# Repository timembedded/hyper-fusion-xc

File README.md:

# hyper-fusion-xc
MSX HyperFusion XC

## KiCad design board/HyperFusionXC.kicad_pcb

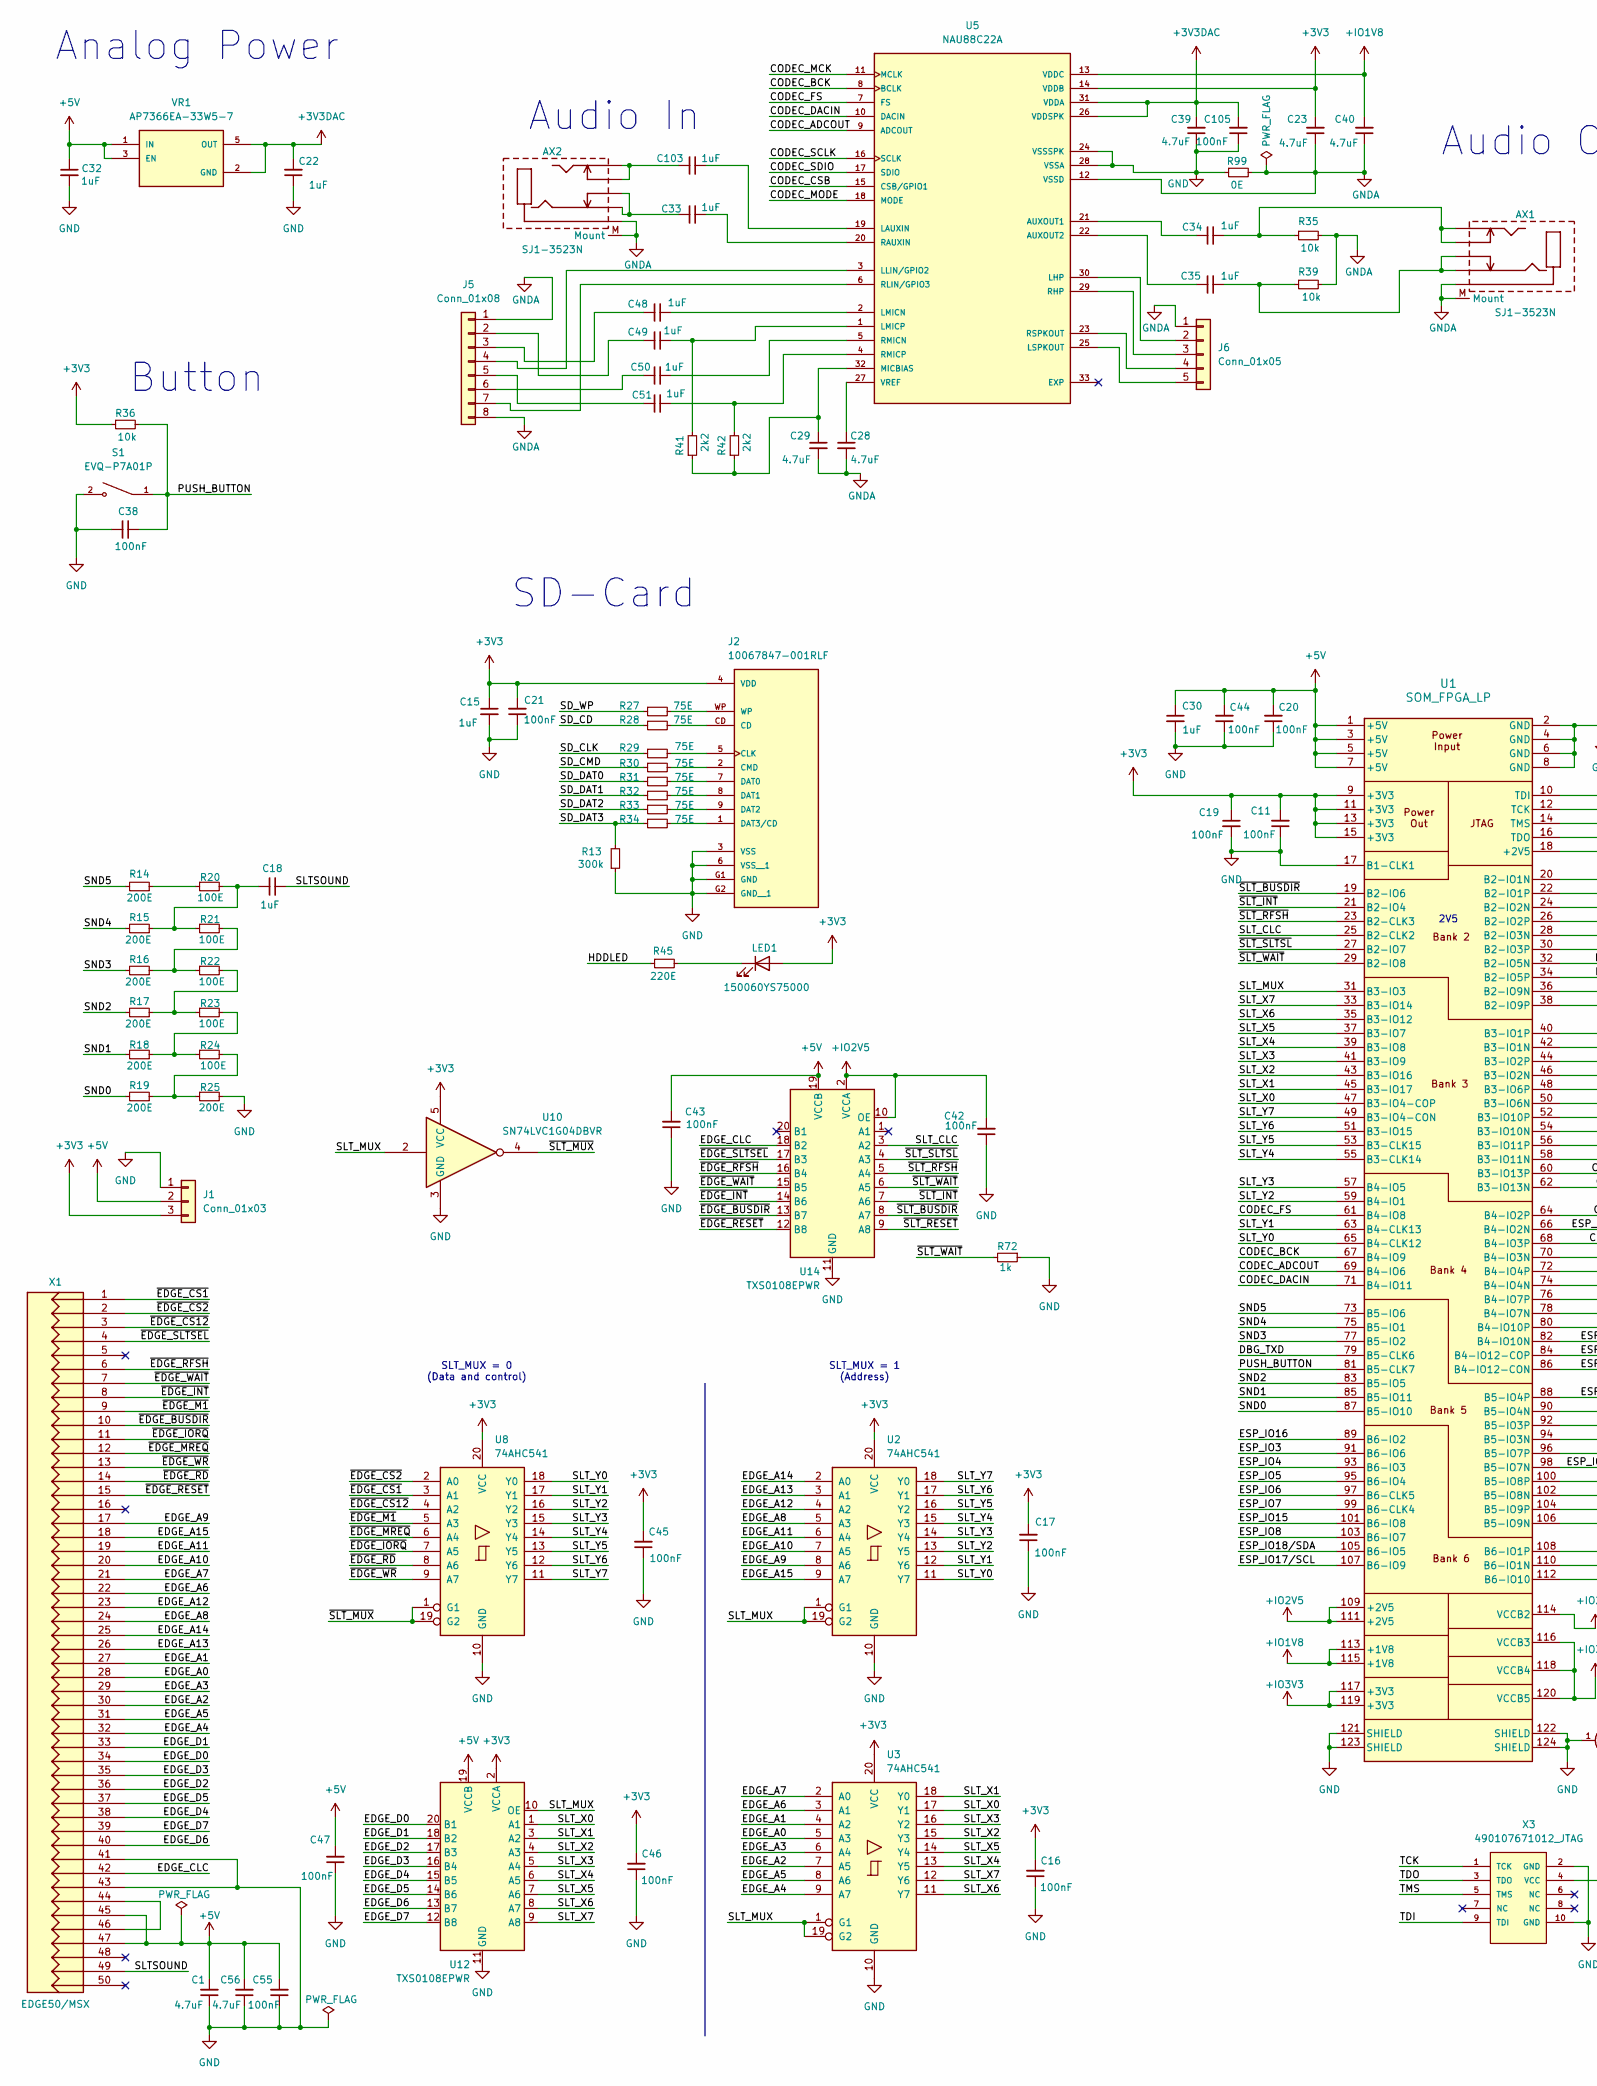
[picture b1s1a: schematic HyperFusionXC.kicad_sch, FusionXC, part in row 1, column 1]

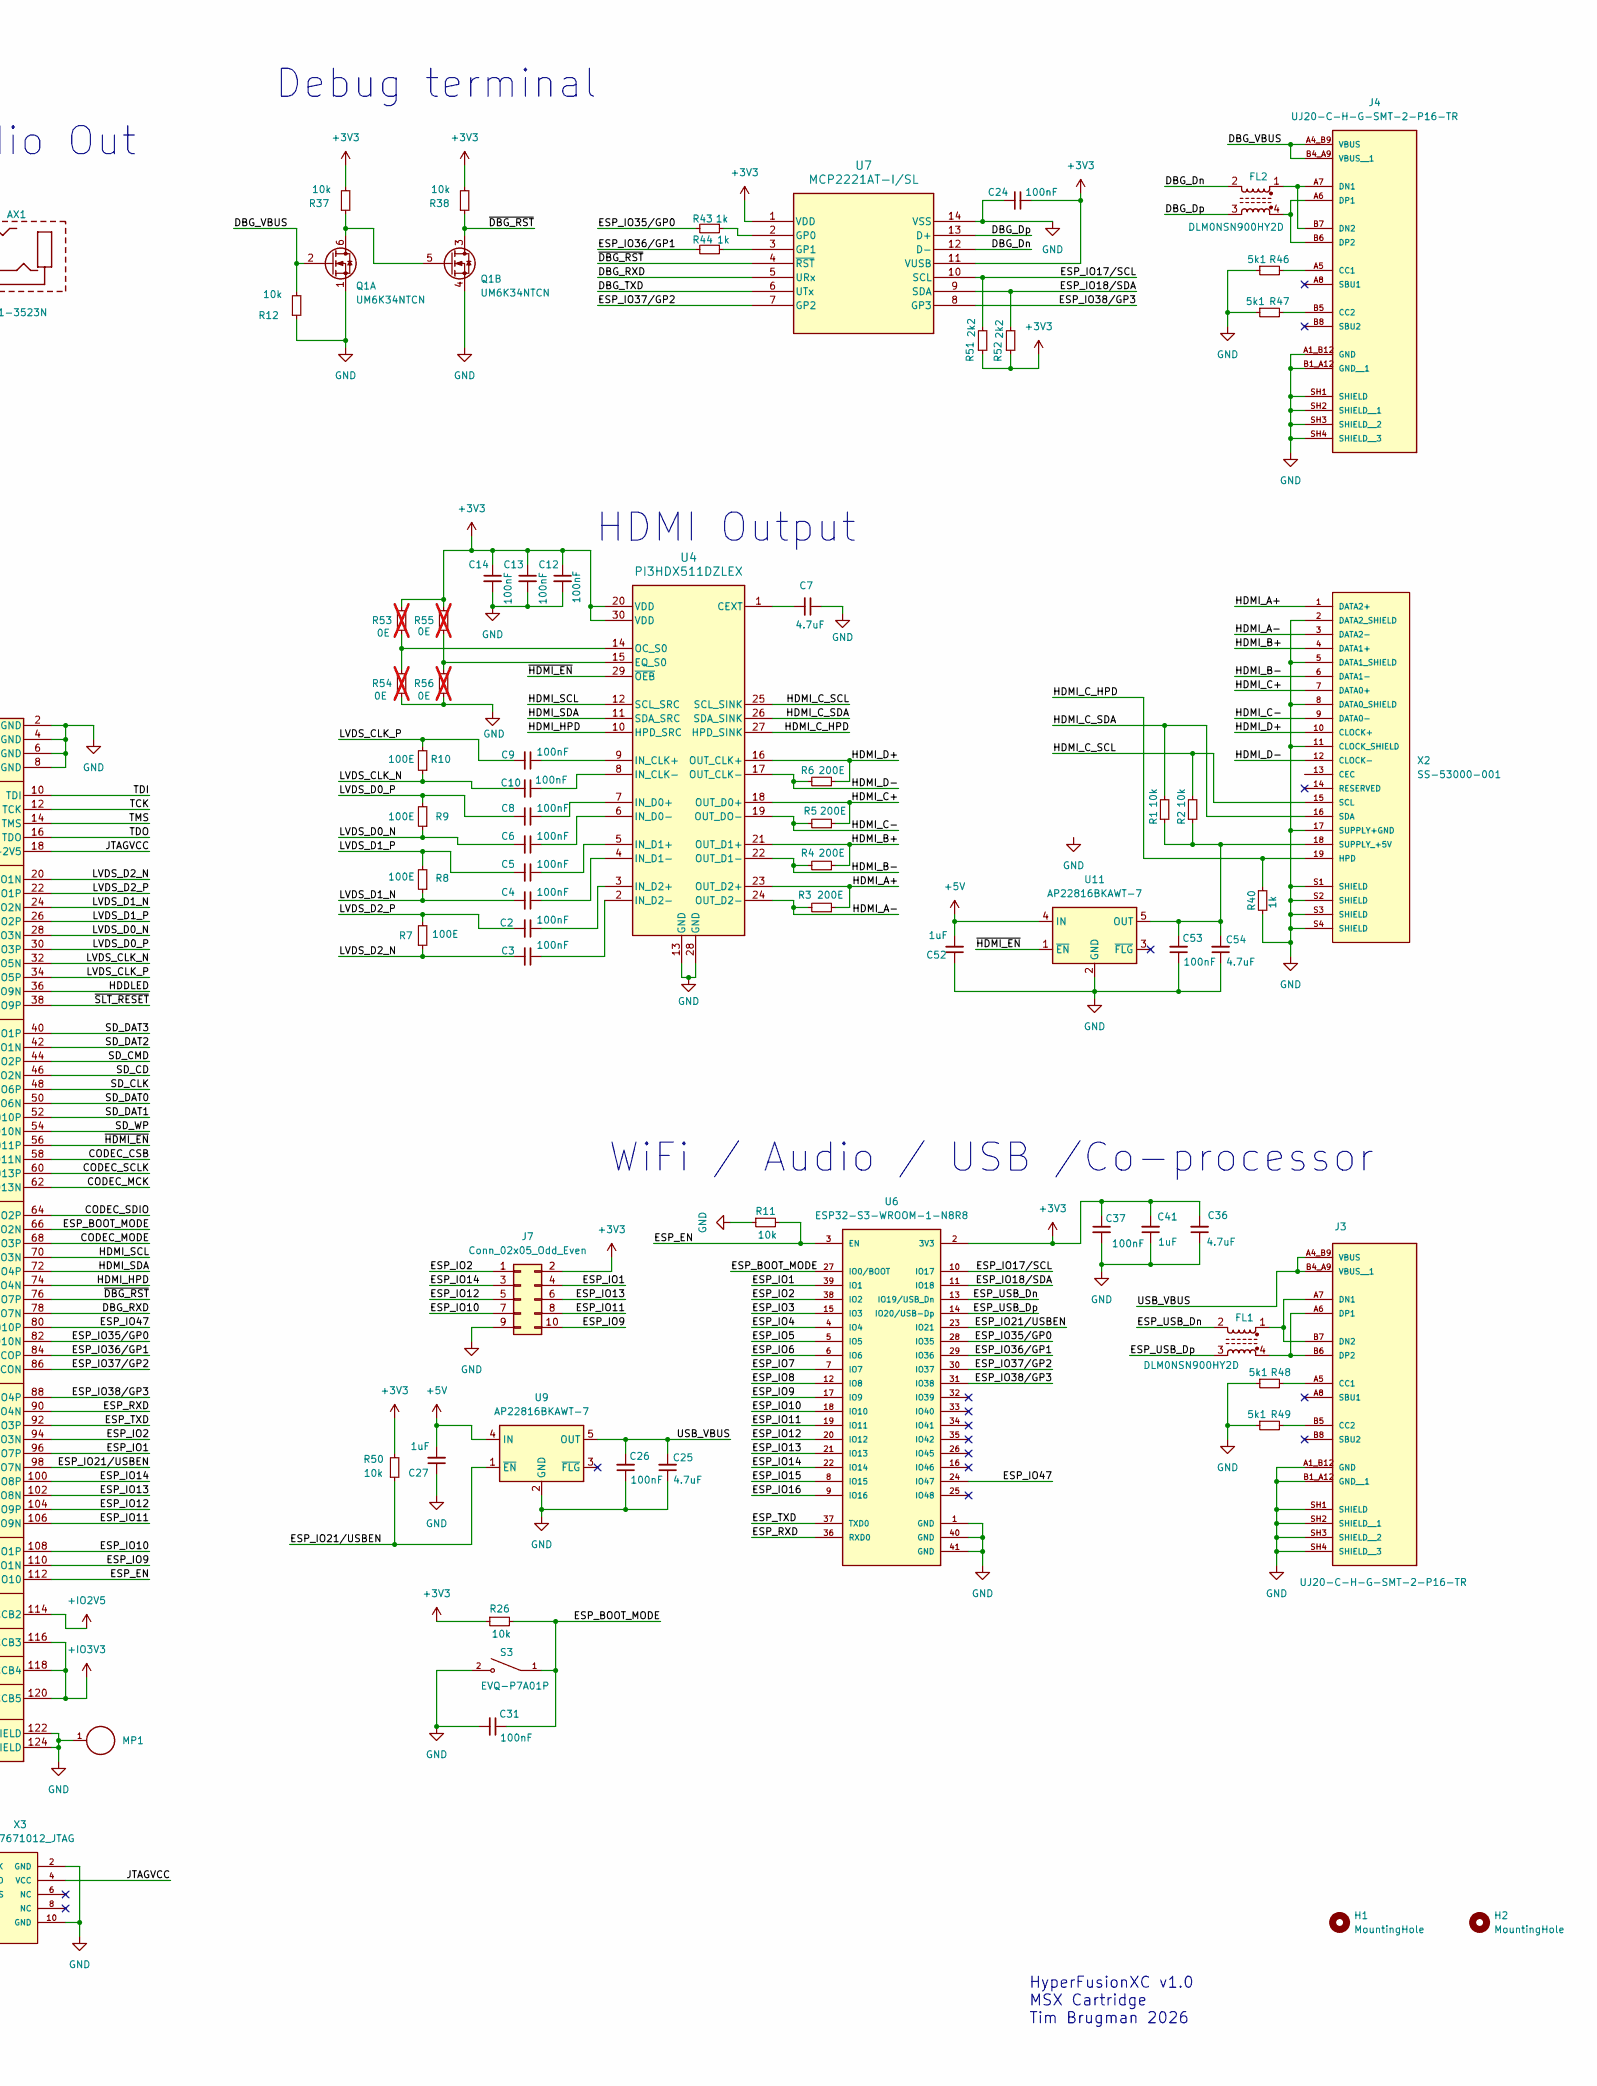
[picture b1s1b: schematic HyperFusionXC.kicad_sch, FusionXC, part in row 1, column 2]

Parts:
AX1, AX2: SJ1-3523N; ST-222_1; DIGIKEY CP1-3523N-ND
C1, C7, C23, C25, C28, C29, C36, C39, C40, C54, C56: 4.7uF; C_0603_1608Metric; DIGIKEY 1276-2087-1-ND
C2, C3, C4, C5, C6, C8, C9, C10, C11, C12, C13, C14, C16, C17, C19, C20, C21, C24, C26, C31, C37, C38, C42, C43, C44, C45, C46, C47, C53, C55, C105: 100nF; C_0603_1608Metric; DIGIKEY 311-1088-1-ND
C15, C18, C22, C27, C30, C32, C33, C34, C35, C41, C48, C49, C50, C51, C52, C103: 1uF; C_0603_1608Metric; DIGIKEY 4988-NMC0603X7R105K6.3TRPFCT-ND
FL1, FL2: DLM0NSN900HY2D; FIL_DLM0NSN900HY2D; DIGIKEY 490-DLM0NSN900HY2DCT-ND
H1, H2: MountingHole
J1: Conn_01x03; PinHeader_1x03_P2.54mm_Vertical
J2: 10067847-001RLF; AMPHENOL_10067847-001RLF; PARTREV K; DIGIKEY 609-3956-1-ND
J3, J4: UJ20-C-H-G-SMT-2-P16-TR; SAMESKY_UJ20-C-H-G-SMT-2-P16-TR; PARTREV 1.0; DIGIKEY 2223-UJ20-C-H-G-SMT-2A-P16-TRCT-ND
J5: Conn_01x08; PinHeader_1x08_P2.00mm_Vertical
J6: Conn_01x05; PinSocket_1x05_P2.00mm_Vertical
J7: Conn_02x05_Odd_Even; PinHeader_2x05_P2.00mm_Vertical
LED1: 150060YS75000; LED_0603_1608Metric_Pad1.05x0.95mm_HandSolder; DIGIKEY 732-4981-1-ND
MP1: M2.5 x 1.5mm; WA-SMSI_9774015151; PART-NUMBER 9774015151R; DIGIKEY 732-7068-1-ND
Q1: UM6K34NTCN; SOT-363_SC-70-6; DIGIKEY UM6K34NTCNCT-ND
R1, R2, R11, R12, R26, R35, R36, R37, R38, R39, R50: 10k; R_0603_1608Metric; DIGIKEY RMCF0603FT10K0CT-ND
R3, R4, R5, R6, R14, R15, R16, R17, R18, R19, R25: 200E; R_0603_1608Metric; DIGIKEY 4463-TFAS0603R2000F-T5CT-ND
R7, R8, R9, R10, R20, R21, R22, R23, R24: 100E; R_0603_1608Metric; DIGIKEY 4463-TFAS0603R1000F-T5CT-ND
R13: 300k; R_0603_1608Metric; DIGIKEY RMCF0603FT300KCT-ND
R27, R28, R29, R30, R31, R32, R33, R34: 75E; R_0603_1608Metric; DIGIKEY RMCF0603FT75R0CT-ND
R40, R43, R44, R72: 1k; R_0603_1608Metric; DIGIKEY RMCF0603FT1K00CT-ND
R41, R42, R51, R52: 2k2; R_0603_1608Metric; DIGIKEY RMCF0603FT2K20CT-ND
R45: 220E; R_0603_1608Metric; DIGIKEY RMCF0603FT220RCT-ND
R46, R47, R48, R49: 5k1; R_0603_1608Metric; DIGIKEY RMCF0603FT5K10CT-ND
R53, R54, R55, R56: 0E; R_0603_1608Metric; DIGIKEY RMCF0603ZT0R00CT-ND; not fitted
R99: 0E; SolderJumper-2_P1.3mm_Bridged_Pad1.0x1.5mm
S1, S3: EVQ-P7A01P; SW_EVQ-P7A01P; PARTREV 2022.4; DIGIKEY P16763CT-ND
U1: SOM_FPGA_LP; DIGIKEY 26-DF40C-120DP-0.4V(51)CT-ND
U2, U3, U8: 74AHC541; TSSOP-20_4.4x6.5mm_P0.65mm; DIGIKEY 1727-3994-1-ND
U4: PI3HDX511DZLEX; Texas_RNH0030A_WQFN-30-1EP_2.5x4.5mm_P0.4mm_EP1.2x3.2mm; DIGIKEY PI3HDX511DZLEXDICT-ND
U5: NAU88C22A; QFN-32-1EP_5x5mm_P0.5mm_EP2.7x2.7mm_ThermalVias; PARTREV 3.3; DIGIKEY NAU88C22YG-ND
U6: ESP32-S3-WROOM-1-N8R8; MODULE_ESP32-S3-WROOM-1-N8R8; DIGIKEY 5407-ESP32-S3-WROOM-1-N8R8CT-ND
U7: MCP2221AT-I/SL; SOIC-14_3.9x8.7mm_P1.27mm; DIGIKEY 150-MCP2221AT-I/SLCT-ND
U9, U11: AP22816BKAWT-7; SOT-23-5; DIGIKEY 31-AP22816BKAWT-7CT-ND
U10: SN74LVC1G04DBVR; SOT-23-5; DIGIKEY 296-11599-1-ND
U12, U14: TXS0108EPWR; TSSOP-20_4.4x6.5mm_P0.65mm; DIGIKEY 296-23011-1-ND
VR1: AP7366EA-33W5-7; SOT-25-AP7366EA; PARTREV 1-2; DIGIKEY 31-AP7366EA-33W5-7CT-ND
X1: EDGE50/MSX; EDGE50_MSX_1
X2: SS-53000-001; STEWART_SS-53000-001; PARTREV A0; DIGIKEY 380-SS-53000-001-ND
X3: 490107671012_JTAG; 490107671012; PARTREV A0; DIGIKEY 732-11636-5-ND

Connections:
+3V3: C11.2, C12.1, C13.1, C14.1, C15.1, C16.2, C17.2, C19.1, C21.2, C23.2, C24.2, C36.2, C37.1, C41.2, C45.2, C46.2, J1.3, J2.4 (VDD), J7.2, LED1.2 (A), R26.1, R36.1, R37.2, R38.2, R50.2, R51.1, R52.1, R53.1, R55.1, U1.9 (+3V3), U1.11 (+3V3), U1.13 (+3V3), U1.15 (+3V3), U2.20 (VCC), U3.20 (VCC), U4.20 (VDD), U4.30 (VDD), U5.14 (VDDB), U6.2 (3V3), U7.1 (VDD), U7.11 (VUSB), U8.20 (VCC), U10.5 (VCC), U12.2 (VCCA)
+3V3DAC: C22.2, C39.2, C105.2, U5.26 (VDDSPK), U5.31 (VDDA), VR1.2 (GND), VR1.5 (OUT)
+5V: C1.2, C20.2, C27.2, C30.1, C32.1, C43.2, C44.2, C47.2, C52.2, C55.2, C56.2, J1.2, U1.1 (+5V), U1.3 (+5V), U1.5 (+5V), U1.7 (+5V), U9.4 (IN), U11.4 (IN), U12.19 (VCCB), U14.19 (VCCB), VR1.1 (IN), VR1.3 (EN), X1.45, X1.47
+IO1V8: C40.2, U1.113 (+1V8), U1.115 (+1V8), U5.13 (VDDC)
+IO2V5: C42.2, U1.109 (+2V5), U1.111 (+2V5), U1.114 (VCCB2), U14.2 (VCCA), U14.10 (OE)
+IO3V3: U1.116 (VCCB3), U1.117 (+3V3), U1.118 (VCCB4), U1.119 (+3V3), U1.120 (VCCB5)
/CODEC_ADCOUT: U1.69 (B4-IO6), U5.9 (ADCOUT)
/CODEC_BCK: U1.67 (B4-IO9), U5.8 (BCLK)
/CODEC_CSB: U1.58 (B3-IO11N), U5.15 (CSB/GPIO1)
/CODEC_DACIN: U1.71 (B4-IO11), U5.10 (DACIN)
/CODEC_FS: U1.61 (B4-IO8), U5.7 (FS)
/CODEC_MCK: U1.62 (B3-IO13N), U5.11 (MCLK)
/CODEC_MODE: U1.68 (B4-IO3P), U5.18 (MODE)
/CODEC_SCLK: U1.60 (B3-IO13P), U5.16 (SCLK)
/CODEC_SDIO: U1.64 (B4-IO2P), U5.17 (SDIO)
/DBG_Dn: FL2.2, U7.12 (D-)
/DBG_Dp: FL2.3, U7.13 (D+)
/DBG_RXD: U1.78 (B4-IO7N), U7.5 (URx)
/DBG_TXD: U1.79 (B5-CLK6), U7.6 (UTx)
/DBG_VBUS: J4.A4_B9 (VBUS), J4.B4_A9 (VBUS__1), Q1.2 (G), R12.2
/EDGE_A0: U3.5 (A3), X1.28
/EDGE_A1: U3.4 (A2), X1.27
/EDGE_A2: U3.7 (A5), X1.30
/EDGE_A3: U3.6 (A4), X1.29
/EDGE_A4: U3.9 (A7), X1.32
/EDGE_A5: U3.8 (A6), X1.31
/EDGE_A6: U3.3 (A1), X1.22
/EDGE_A7: U3.2 (A0), X1.21
/EDGE_A8: U2.5 (A3), X1.24
/EDGE_A9: U2.8 (A6), X1.17
/EDGE_A10: U2.7 (A5), X1.20
/EDGE_A11: U2.6 (A4), X1.19
/EDGE_A12: U2.4 (A2), X1.23
/EDGE_A13: U2.3 (A1), X1.26
/EDGE_A14: U2.2 (A0), X1.25
/EDGE_A15: U2.9 (A7), X1.18
/EDGE_CLC: U14.18 (B2), X1.42
/EDGE_D0: U12.20 (B1), X1.34
/EDGE_D1: U12.18 (B2), X1.33
/EDGE_D2: U12.17 (B3), X1.36
/EDGE_D3: U12.16 (B4), X1.35
/EDGE_D4: U12.15 (B5), X1.38
/EDGE_D5: U12.14 (B6), X1.37
/EDGE_D6: U12.13 (B7), X1.40
/EDGE_D7: U12.12 (B8), X1.39
/ESP_BOOT_MODE: C31.1, R26.2, S3.1, U1.66 (B4-IO2N), U6.27 (IO0/BOOT)
/ESP_EN: R11.2, U1.112 (B6-IO10), U6.3 (EN)
/ESP_IO1: J7.4, U1.96 (B5-IO7P), U6.39 (IO1)
/ESP_IO2: J7.1, U1.94 (B5-IO3N), U6.38 (IO2)
/ESP_IO3: U1.91 (B6-IO6), U6.15 (IO3)
/ESP_IO4: U1.93 (B6-IO3), U6.4 (IO4)
/ESP_IO5: U1.95 (B6-IO4), U6.5 (IO5)
/ESP_IO6: U1.97 (B6-CLK5), U6.6 (IO6)
/ESP_IO7: U1.99 (B6-CLK4), U6.7 (IO7)
/ESP_IO8: U1.103 (B6-IO7), U6.12 (IO8)
/ESP_IO9: J7.10, U1.110 (B6-IO1N), U6.17 (IO9)
/ESP_IO10: J7.7, U1.108 (B6-IO1P), U6.18 (IO10)
/ESP_IO11: J7.8, U1.106 (B5-IO9N), U6.19 (IO11)
/ESP_IO12: J7.5, U1.104 (B5-IO9P), U6.20 (IO12)
/ESP_IO13: J7.6, U1.102 (B5-IO8N), U6.21 (IO13)
/ESP_IO14: J7.3, U1.100 (B5-IO8P), U6.22 (IO14)
/ESP_IO15: U1.101 (B6-IO8), U6.8 (IO15)
/ESP_IO16: U1.89 (B6-IO2), U6.9 (IO16)
/ESP_IO17/SCL: R51.2, U1.107 (B6-IO9), U6.10 (IO17), U7.10 (SCL)
/ESP_IO18/SDA: R52.2, U1.105 (B6-IO5), U6.11 (IO18), U7.9 (SDA)
/ESP_IO21/USBEN: R50.1, U1.98 (B5-IO7N), U6.23 (IO21), U9.1 (~EN)
/ESP_IO35/GP0: R43.2, U1.82 (B4-IO10N), U6.28 (IO35)
/ESP_IO36/GP1: R44.2, U1.84 (B4-IO12-COP), U6.29 (IO36)
/ESP_IO37/GP2: U1.86 (B4-IO12-CON), U6.30 (IO37), U7.7 (GP2)
/ESP_IO38/GP3: U1.88 (B5-IO4P), U6.31 (IO38), U7.8 (GP3)
/ESP_IO47: U1.80 (B4-IO10P), U6.24 (IO47)
/ESP_RXD: U1.90 (B5-IO4N), U6.36 (RXD0)
/ESP_TXD: U1.92 (B5-IO3P), U6.37 (TXD0)
/ESP_USB_Dn: FL1.2, U6.13 (IO19/USB_Dn)
/ESP_USB_Dp: FL1.3, U6.14 (IO20/USB-Dp)
/HDDLED: R45.1, U1.36 (B2-IO9N)
/HDMI_A+: R3.1, U4.23 (OUT_D2+), X2.1 (DATA2+)
/HDMI_A-: R3.2, U4.24 (OUT_D2-), X2.3 (DATA2-)
/HDMI_B+: R4.1, U4.21 (OUT_D1+), X2.4 (DATA1+)
/HDMI_B-: R4.2, U4.22 (OUT_D1-), X2.6 (DATA1-)
/HDMI_C+: R5.1, U4.18 (OUT_D0+), X2.7 (DATA0+)
/HDMI_C-: R5.2, U4.19 (OUT_DO-), X2.9 (DATA0-)
/HDMI_C_HPD: R40.1, U4.27 (HPD_SINK), X2.19 (HPD)
/HDMI_C_SCL: R2.2, U4.25 (SCL_SINK), X2.15 (SCL)
/HDMI_C_SDA: R1.2, U4.26 (SDA_SINK), X2.16 (SDA)
/HDMI_D+: R6.1, U4.16 (OUT_CLK+), X2.10 (CLOCK+)
/HDMI_D-: R6.2, U4.17 (OUT_CLK-), X2.12 (CLOCK-)
/HDMI_HPD: U1.74 (B4-IO4N), U4.10 (HPD_SRC)
/HDMI_SCL: U1.70 (B4-IO3N), U4.12 (SCL_SRC)
/HDMI_SDA: U1.72 (B4-IO4P), U4.11 (SDA_SRC)
/JTAGVCC: U1.18 (+2V5), X3.4 (VCC)
/LVDS_CLK_N: C10.2, R10.1, U1.32 (B2-IO5N)
/LVDS_CLK_P: C9.2, R10.2, U1.34 (B2-IO5P)
/LVDS_D0_N: C6.2, R9.1, U1.28 (B2-IO3N)
/LVDS_D0_P: C8.2, R9.2, U1.30 (B2-IO3P)
/LVDS_D1_N: C4.2, R8.1, U1.24 (B2-IO2N)
/LVDS_D1_P: C5.2, R8.2, U1.26 (B2-IO2P)
/LVDS_D2_N: C3.2, R7.1, U1.20 (B2-IO1N)
/LVDS_D2_P: C2.2, R7.2, U1.22 (B2-IO1P)
/PUSH_BUTTON: C38.1, R36.2, S1.1, U1.81 (B5-CLK7)
/SD_CD: R28.1, U1.46 (B3-IO2N)
/SD_CLK: R29.1, U1.48 (B3-IO6P)
/SD_CMD: R30.1, U1.44 (B3-IO2P)
/SD_DAT0: R31.1, U1.50 (B3-IO6N)
/SD_DAT1: R32.1, U1.52 (B3-IO10P)
/SD_DAT2: R33.1, U1.42 (B3-IO1N)
/SD_DAT3: R13.2, R34.1, U1.40 (B3-IO1P)
/SD_WP: R27.1, U1.54 (B3-IO10N)
/SLTSOUND: C18.1, X1.49
/SLT_CLC: U1.25 (B2-CLK2), U14.3 (A2)
/SLT_MUX: U1.31 (B3-IO3), U2.1 (G1), U2.19 (G2), U3.1 (G1), U3.19 (G2), U10.2, U12.10 (OE)
/SLT_X0: U1.47 (B3-IO4-COP), U3.17 (Y1), U12.1 (A1)
/SLT_X1: U1.45 (B3-IO17), U3.18 (Y0), U12.3 (A2)
/SLT_X2: U1.43 (B3-IO16), U3.15 (Y3), U12.4 (A3)
/SLT_X3: U1.41 (B3-IO9), U3.16 (Y2), U12.5 (A4)
/SLT_X4: U1.39 (B3-IO8), U3.13 (Y5), U12.6 (A5)
/SLT_X5: U1.37 (B3-IO7), U3.14 (Y4), U12.7 (A6)
/SLT_X6: U1.35 (B3-IO12), U3.11 (Y7), U12.8 (A7)
/SLT_X7: U1.33 (B3-IO14), U3.12 (Y6), U12.9 (A8)
/SLT_Y0: U1.65 (B4-CLK12), U2.11 (Y7), U8.18 (Y0)
/SLT_Y1: U1.63 (B4-CLK13), U2.12 (Y6), U8.17 (Y1)
/SLT_Y2: U1.59 (B4-IO1), U2.13 (Y5), U8.16 (Y2)
/SLT_Y3: U1.57 (B4-IO5), U2.14 (Y4), U8.15 (Y3)
/SLT_Y4: U1.55 (B3-CLK14), U2.15 (Y3), U8.14 (Y4)
/SLT_Y5: U1.53 (B3-CLK15), U2.16 (Y2), U8.13 (Y5)
/SLT_Y6: U1.51 (B3-IO15), U2.17 (Y1), U8.12 (Y6)
/SLT_Y7: U1.49 (B3-IO4-CON), U2.18 (Y0), U8.11 (Y7)
/SND0: R19.2, U1.87 (B5-IO10)
/SND1: R18.2, U1.85 (B5-IO11)
/SND2: R17.2, U1.83 (B5-IO5)
/SND3: R16.2, U1.77 (B5-IO2)
/SND4: R15.2, U1.75 (B5-IO1)
/SND5: R14.2, U1.73 (B5-IO6)
/TCK: U1.12 (TCK), X3.1 (TCK)
/TDI: U1.10 (TDI), X3.9 (TDI)
/TDO: U1.16 (TDO), X3.3 (TDO)
/TMS: U1.14 (TMS), X3.5 (TMS)
/USB_VBUS: C25.2, C26.2, J3.A4_B9 (VBUS), J3.B4_A9 (VBUS__1), U9.5 (OUT)
/~DBG_RST: Q1.3 (D), R38.1, U1.76 (B4-IO7P), U7.4 (~RST)
/~EDGE_BUSDIR: U14.13 (B7), X1.10
/~EDGE_CS1: U8.3 (A1), X1.1
/~EDGE_CS2: U8.2 (A0), X1.2
/~EDGE_CS12: U8.4 (A2), X1.3
/~EDGE_INT: U14.14 (B6), X1.8
/~EDGE_IORQ: U8.7 (A5), X1.11
/~EDGE_M1: U8.5 (A3), X1.9
/~EDGE_MREQ: U8.6 (A4), X1.12
/~EDGE_RD: U8.8 (A6), X1.14
/~EDGE_RESET: U14.12 (B8), X1.15
/~EDGE_RFSH: U14.16 (B4), X1.6
/~EDGE_SLTSEL: U14.17 (B3), X1.4
/~EDGE_WAIT: U14.15 (B5), X1.7
/~EDGE_WR: U8.9 (A7), X1.13
/~HDMI_EN: U1.56 (B3-IO11P), U4.29 (~OEB), U11.1 (~EN)
/~SLT_BUSDIR: U1.19 (B2-IO6), U14.8 (A7)
/~SLT_INT: U1.21 (B2-IO4), U14.7 (A6)
/~SLT_MUX: U8.1 (G1), U8.19 (G2), U10.4
/~SLT_RESET: U1.38 (B2-IO9P), U14.9 (A8)
/~SLT_RFSH: U1.23 (B2-CLK3), U14.5 (A4)
/~SLT_SLTSL: U1.27 (B2-IO7), U14.4 (A3)
/~SLT_WAIT: R72.2, U1.29 (B2-IO8), U14.6 (A5)
GND: C1.1, C7.1, C11.1, C12.2, C13.2, C14.2, C15.2, C16.1, C17.1, C19.2, C20.1, C21.1, C22.1, C24.1, C25.1, C26.1, C27.1, C30.2, C31.2, C32.2, C36.1, C37.2, C38.2, C39.1, C41.1, C42.1, C43.1, C44.1, C45.1, C46.1, C47.1, C52.1, C53.1, C54.1, C55.1, C56.1, C105.1, J1.1, J2.3 (VSS), J2.6 (VSS__1), J2.G1 (GND), J2.G2 (GND__1), J3.A1_B12 (GND), J3.B1_A12 (GND__1), J3.SH1 (SHIELD), J3.SH2 (SHIELD__1), J3.SH3 (SHIELD__2), J3.SH4 (SHIELD__3), J4.A1_B12 (GND), J4.B1_A12 (GND__1), J4.SH1 (SHIELD), J4.SH2 (SHIELD__1), J4.SH3 (SHIELD__2), J4.SH4 (SHIELD__3), J7.9, MP1.1, Q1.1 (S), Q1.4 (S), R11.1, R12.1, R13.1, R25.2, R40.2, R46.1, R47.1, R48.1, R49.1, R54.2, R56.2, R72.1, R99.1, S1.2, S3.2, U1.2 (GND), U1.4 (GND), U1.6 (GND), U1.8 (GND), U1.17 (B1-CLK1), U1.121 (SHIELD), U1.122 (SHIELD), U1.123 (SHIELD), U1.124 (SHIELD), U2.10 (GND), U3.10 (GND), U4.13 (GND), U4.28 (GND), U5.24 (VSSSPK), U5.28 (VSSA), U6.1 (GND), U6.40 (GND), U6.41 (GND), U7.14 (VSS), U8.10 (GND), U9.2 (GND), U10.3 (GND), U11.2 (GND), U12.11 (GND), U14.11 (GND), X1.41, X1.43, X2.2 (DATA2_SHIELD), X2.5 (DATA1_SHIELD), X2.8 (DATA0_SHIELD), X2.11 (CLOCK_SHIELD), X2.17 (SUPPLY+GND), X2.S1 (SHIELD), X2.S2 (SHIELD), X2.S3 (SHIELD), X2.S4 (SHIELD), X3.2 (GND), X3.10 (GND)
GNDA: AX1.1, AX1.M (Mount), AX2.1, AX2.M (Mount), C23.1, C28.2, C29.2, C40.1, J5.1, J5.8, J6.1, R35.2, R39.2, R99.2, U5.12 (VSSD)
unnamed: AX1.2, AX1.3, C35.1, R39.1
unnamed: AX1.4, AX1.5, C34.1, R35.1
unnamed: AX2.2, AX2.3, C33.2
unnamed: AX2.4, AX2.5, C103.2
unnamed: C18.2, R15.1, R20.2, R21.1
unnamed: J2.5 (CLK), R29.2
unnamed: J2.2 (CMD), R30.2
unnamed: J2.7 (DAT0), R31.2
unnamed: J2.8 (DAT1), R32.2
unnamed: J2.9 (DAT2), R33.2
unnamed: J2.1 (DAT3/CD), R34.2
unnamed: J2.CD, R28.2
unnamed: J2.WP, R27.2
unnamed: J3.A5 (CC1), R48.2
unnamed: J3.B5 (CC2), R49.2
unnamed: FL1.1, J3.A7 (DN1), J3.B7 (DN2)
unnamed: FL1.4, J3.A6 (DP1), J3.B6 (DP2)
unnamed: J4.A5 (CC1), R46.2
unnamed: J4.B5 (CC2), R47.2
unnamed: FL2.1, J4.A7 (DN1), J4.B7 (DN2)
unnamed: FL2.4, J4.A6 (DP1), J4.B6 (DP2)
unnamed: C49.2, J5.2
unnamed: C48.2, J5.3
unnamed: J5.4, U5.3 (LLIN/GPIO2)
unnamed: C51.2, J5.5
unnamed: C50.2, J5.6
unnamed: J5.7, U5.6 (RLIN/GPIO3)
unnamed: J6.2, U5.30 (LHP)
unnamed: J6.3, U5.29 (RHP)
unnamed: J6.4, U5.23 (RSPKOUT)
unnamed: J6.5, U5.25 (LSPKOUT)
unnamed: LED1.1 (K), R45.2
unnamed: Q1.5 (G), Q1.6 (D), R37.1
unnamed: R14.1, R20.1
unnamed: R16.1, R21.2, R22.1
unnamed: R17.1, R22.2, R23.1
unnamed: R18.1, R23.2, R24.1
unnamed: R19.1, R24.2, R25.1
unnamed: C7.2, U4.1 (CEXT)
unnamed: R55.2, R56.1, U4.15 (EQ_S0)
unnamed: C9.1, U4.9 (IN_CLK+)
unnamed: C10.1, U4.8 (IN_CLK-)
unnamed: C8.1, U4.7 (IN_D0+)
unnamed: C6.1, U4.6 (IN_D0-)
unnamed: C5.1, U4.5 (IN_D1+)
unnamed: C4.1, U4.4 (IN_D1-)
unnamed: C2.1, U4.3 (IN_D2+)
unnamed: C3.1, U4.2 (IN_D2-)
unnamed: R53.2, R54.1, U4.14 (OC_S0)
unnamed: C34.2, U5.21 (AUXOUT1)
unnamed: C35.2, U5.22 (AUXOUT2)
unnamed: C103.1, U5.19 (LAUXIN)
unnamed: C48.1, U5.2 (LMICN)
unnamed: C49.1, R41.2, U5.1 (LMICP)
unnamed: C29.1, R41.1, R42.1, U5.32 (MICBIAS)
unnamed: C33.1, U5.20 (RAUXIN)
unnamed: C50.1, U5.5 (RMICN)
unnamed: C51.1, R42.2, U5.4 (RMICP)
unnamed: C28.1, U5.27 (VREF)
unnamed: R43.1, U7.2 (GP0)
unnamed: R44.1, U7.3 (GP1)
unnamed: C53.2, C54.2, R1.1, R2.1, U11.5 (OUT), X2.18 (SUPPLY_+5V)
unnamed: X1.44, X1.46

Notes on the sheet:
WiFi / Audio / USB /Co-processor
Debug terminal
SD-Card
HDMI Output
Analog Power
SLT_MUX = 0 (Data and control)
SLT_MUX = 1 (Address)
Audio In
Audio Out
Button
2V5
HyperFusionXC v1.0 MSX Cartridge Tim Brugman 2026

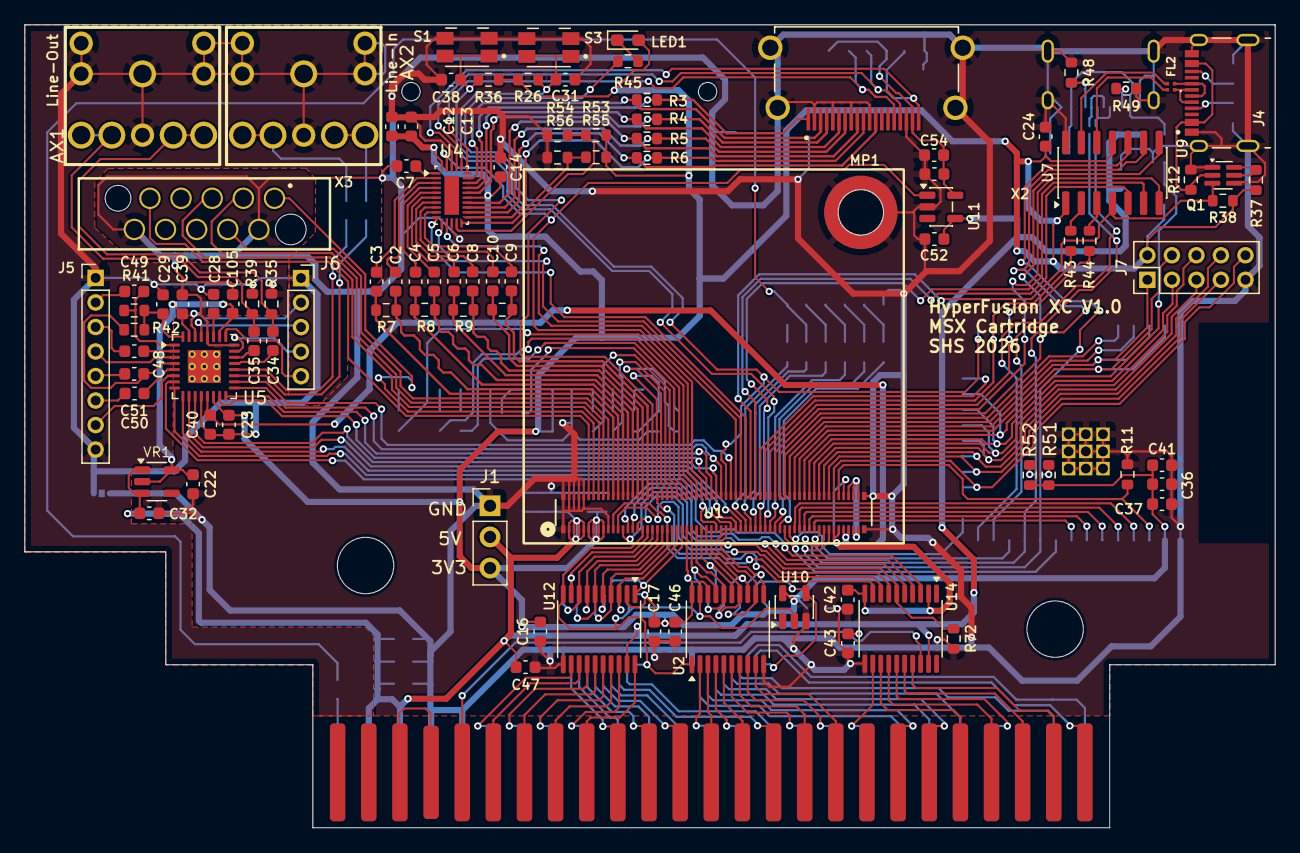
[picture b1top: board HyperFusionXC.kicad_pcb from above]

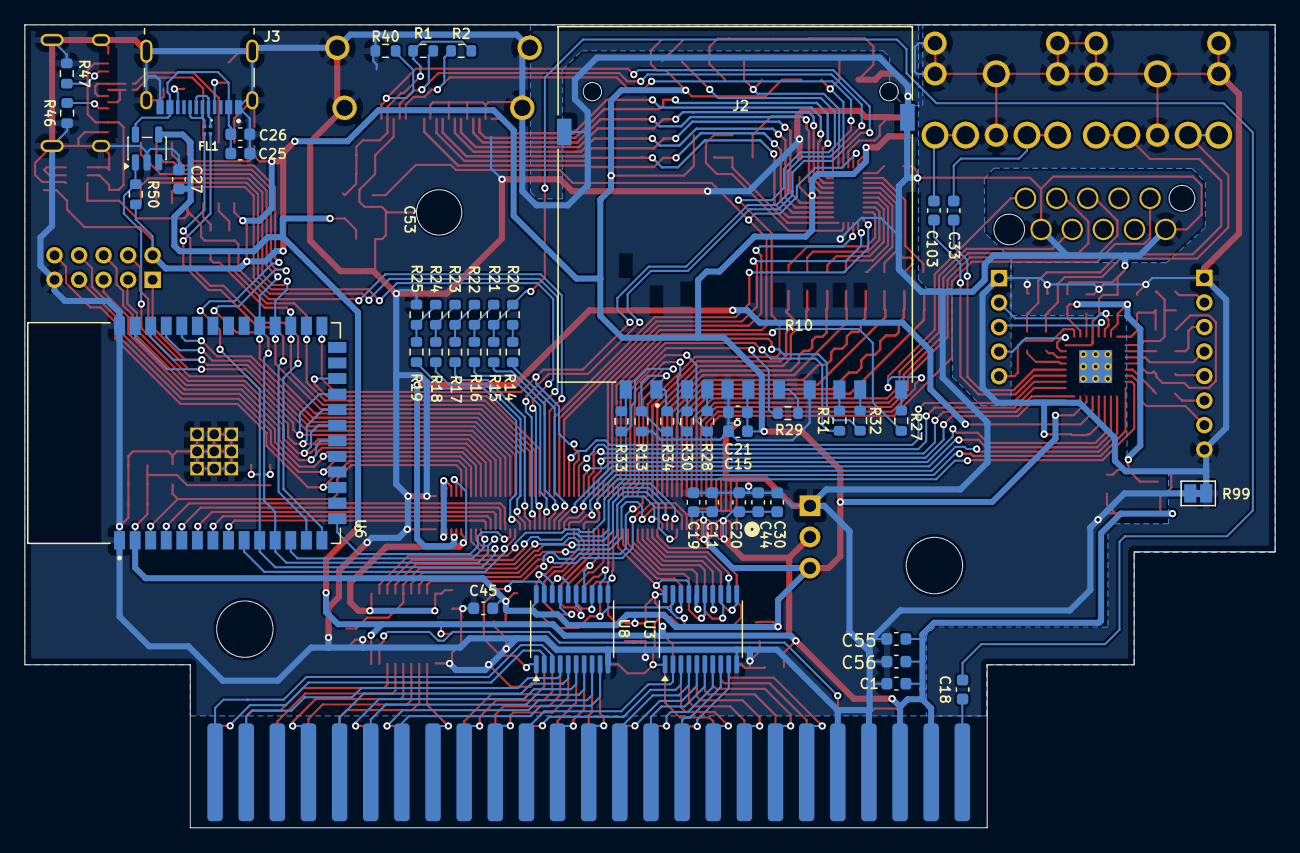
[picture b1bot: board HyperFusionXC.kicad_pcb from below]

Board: 2 copper layers, 102.0 x 65.5 mm, 151 parts (52 on the bottom side), 226 nets.

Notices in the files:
firmware/proto/fpga.qsf:
Copyright (C) 1991-2009 Altera Corporation
